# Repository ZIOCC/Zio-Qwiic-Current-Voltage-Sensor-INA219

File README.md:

# Zio-Qwiic-Current-Voltage-Sensor-INA219

> This product can be available for purchase [here](https://www.smart-prototyping.com/Zio-Qwiic-Current-Voltage-Sensor-INA219).

#### Description

A current and power monitor on a breakout board! This board right here features an INA219, enabling to read DC current drop and power over I2C with a high precision, up to 1%.

This board can be used for many applications such as estimating battery life, measuring battery levels, tracking solar power generation or monitoring the amount and cost of electricity consumption. 

It can measure voltage up to +26VDC, incorporating a 0.1 ohm shunt resistor for measuring the current (labeled at R100). The INA219 has a very precise rate on measuring voltage draw over the shunt. The current flow is determined along the voltage drop over the shunt, based on Ohm’s law. With the voltage and current known, the power can be also calculated. 

The maximum voltage drop that the INA219 can measure is ±320mV, thence the maximum amperage is 3.2A. The shunt resistor can actually be replaced to have a higher allowance (only for experienced users). 

As the INA219 supports the I2C interface it makes it a lot easier to daisy chain multiple devices and get the data though the Qwiic connector. Pretty cool as we can get the actual numbers for voltage, current and power in its corresponding units. 

To take a measurement on any load, just connect the positive terminal of the power source to VIN+ port. Then connect one of the leads from the load to the VIN- terminal. Connect the other lead to the ground to the power supply negative terminal. Here we go, we have a closed circuit with current flowing to take the measurements.

We also provided the pinout to be able to attach the sensor to a breadboard in case you need it. 

#### Specification

* Operation Voltage: 3.3V
* Bus Voltage: 0- 26V
* Max Current: 3.2A
* Interface: I2C
* IC: INA219
* I2C Address: 0x40, 0x41, 0x44, 0x45, (Default 0x40)
* Dimensions: 25.4 x 25.4mm
* Weight: 3.0g

#### Links

* [Eagle File and Schematic](https://github.com/ZIOCC/Zio-Qwiic-Current-Voltage-Sensor-INA219)
* [Library link](https://github.com/adafruit/Adafruit_INA219)
* [INA219 Datasheet](http://www.ti.com/lit/ds/symlink/ina219.pdf)

> ###### About Zio
> Zio is a new line of open sourced, compact, and grid layout boards, fully integrated for Arduino and Qwiic ecosystem. Designed ideally for wearables, robotics, small-space limitations or other on the go projects. Check out other awesome Zio products [here](https://www.smart-prototyping.com/Zio).

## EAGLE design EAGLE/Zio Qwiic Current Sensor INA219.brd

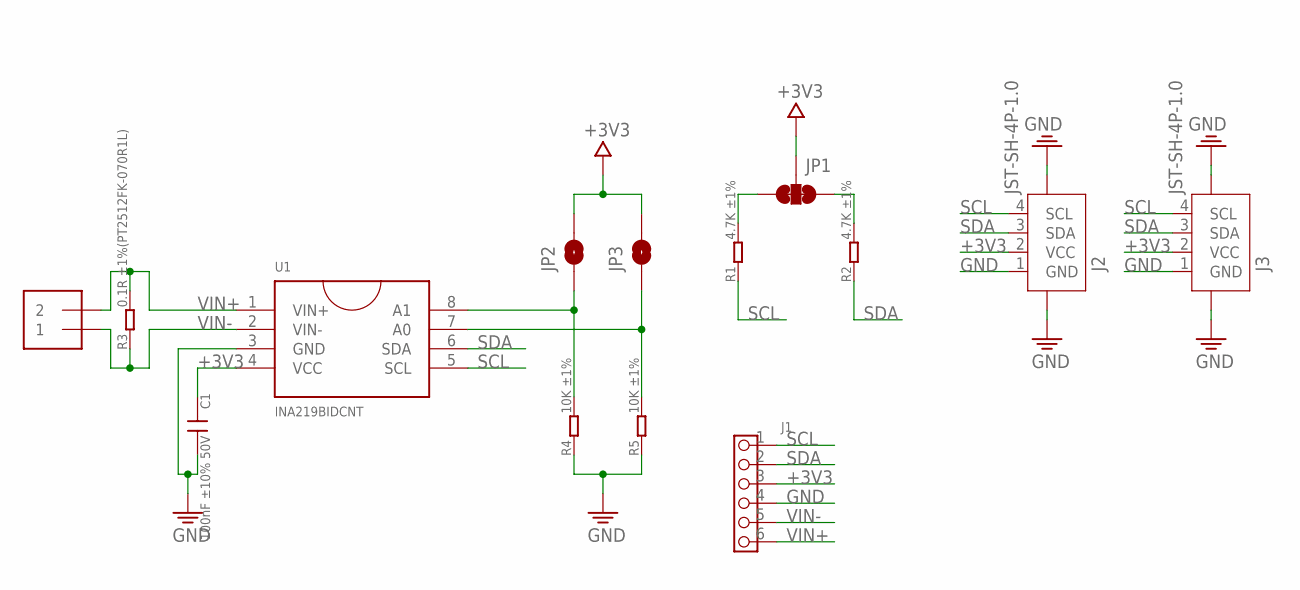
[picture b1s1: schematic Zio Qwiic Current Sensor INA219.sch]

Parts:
C1: 100nF ±10% 50V; C0603
J1: HEADER-6P-60/35MIL; 6P-2.54-60/35MIL
J2, J3: JST-SH-4P-1.0; JST-SH-4P
J6: TERMBLOCK_1X2-3.5MM; 1X2-3.5MM
JP1: SMT-JUMPER_3_2-NC_TRACE
JP2, JP3: JUMPER-SMT_2_NC_PASTE_NOCREM; SMT-JUMPER_2_NC_PASTE_SILK_NOCREM
R1, R2: 4.7K ±1%; R0603
R3: 0.1R ±1%(PT2512FK-070R1L); R2512
R4, R5: 10K ±1%; R0603
U1: INA219BIDCNT; SOT23-8

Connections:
+3V3: C1.1, J1.3, J2.2 (VCC), J3.2 (VCC), JP1.2, JP2.2, JP3.2, U1.4 (VCC)
GND: C1.2, J1.4, J2.1 (GND), J2.NC1 (5), J2.NC2 (6), J3.1 (GND), J3.NC1 (5), J3.NC2 (6), R4.1, R5.1, U1.3 (GND)
unnamed: JP2.1, R4.2, U1.8 (A1)
unnamed: JP3.1, R5.2, U1.7 (A0)
unnamed: JP1.3, R1.2
unnamed: JP1.1, R2.2
SCL: J1.1, J2.4 (SCL), J3.4 (SCL), R1.1, U1.5 (SCL)
SDA: J1.2, J2.3 (SDA), J3.3 (SDA), R2.1, U1.6 (SDA)
VIN+: J1.6, J6.2, R3.2, U1.1 (VIN+)
VIN-: J1.5, J6.1, R3.1, U1.2 (VIN-)

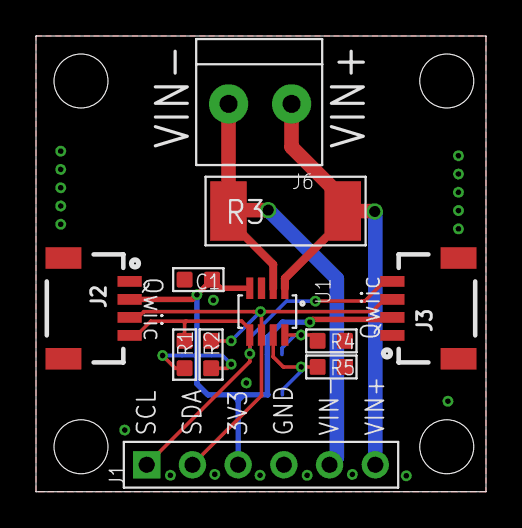
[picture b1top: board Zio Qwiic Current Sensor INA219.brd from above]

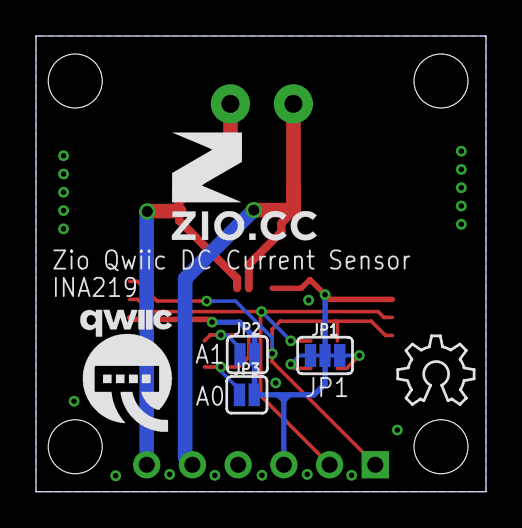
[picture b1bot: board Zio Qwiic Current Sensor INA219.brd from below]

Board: 2 copper layers, 25.0 x 25.3 mm, 17 parts (6 on the bottom side), 10 nets.

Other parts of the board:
U$3: 6MM
U$4: QWIIC-LOGO-MEDIUM
U$5: OSHW_6X150_NOTEXT
